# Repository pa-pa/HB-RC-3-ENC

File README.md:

# HB-RC-3-ENC
Homematic Remote Control for Dimmer

[HB-RC-3-ENC.ino](https://github.com/pa-pa/AskSinPP/tree/master/examples/custom/HB-RC-3-ENC)

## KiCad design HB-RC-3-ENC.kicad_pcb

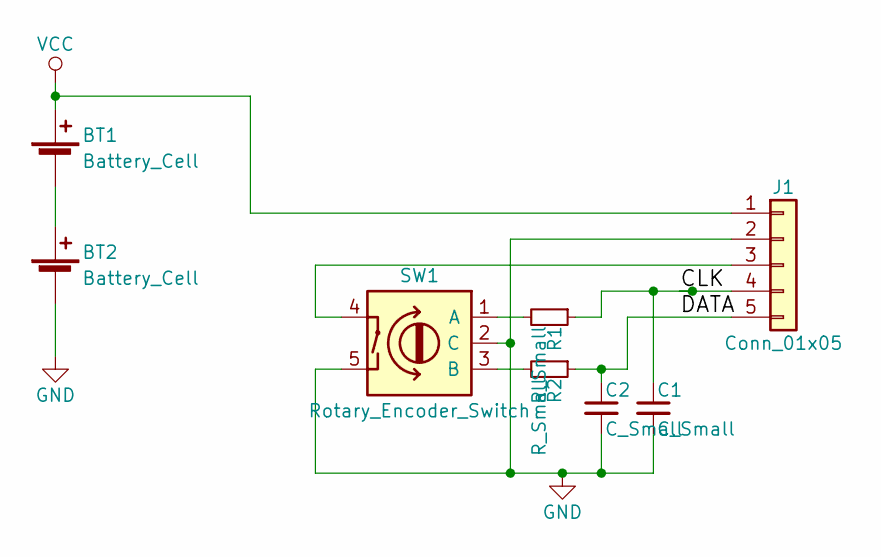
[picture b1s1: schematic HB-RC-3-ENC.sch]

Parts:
BT1, BT2: Battery_Cell; AAA_Holder_Keystone2466
C1, C2: C_Small; C_Disc_D3.0mm_W1.6mm_P2.50mm
J1: Conn_01x05; Pin_Header_Straight_1x05_Pitch2.54mm
R1, R2: R_Small; R_Axial_DIN0204_L3.6mm_D1.6mm_P2.54mm_Vertical
SW1: Rotary_Encoder_Switch; RotaryEncoder_Alps_EC11E-Switch_Vertical_H20mm_2

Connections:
/CLK: C1.1, J1.4, R1.1
/DATA: C2.1, J1.5, R2.1
GND: BT2.2 (-), C1.2, C2.2, J1.2, SW1.2 (C), SW1.5
unnamed: BT1.2 (-), BT2.1 (+)
unnamed: J1.3, SW1.4
unnamed: R1.2, SW1.1 (A)
unnamed: R2.2, SW1.3 (B)
VCC: BT1.1 (+), J1.1

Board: 2 copper layers, 8 parts (1 on the bottom side), 8 nets, no tracks yet.

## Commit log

2019-01-10 initial checkin
